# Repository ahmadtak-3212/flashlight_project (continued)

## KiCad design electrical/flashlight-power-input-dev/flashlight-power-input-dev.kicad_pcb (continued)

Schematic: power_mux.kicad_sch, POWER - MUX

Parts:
C_U13_1, C_U13_2, C_U17_2, C_U17_3: 1u; C_0402_1005Metric; LCSC C1525
C_U14_1: 100n; C_0402_1005Metric; LCSC C1525
C_U16_1, C_U16_2: 10u; C_0603_1608Metric; LCSC C1525
D_Q1_1, D_Q2_1: GREEN; LED_0603_1608Metric; LCSC C2286
L_U16_1: 4.7u; IND-SMD_L3.0-W3.0_SMNR3015; MPN SMNR3015-4R7MT; LCSC Part C23960
Q1, Q2: 2N7002; SOT-23
R_Q1_1, R_Q2_1: 1k; R_0402_1005Metric; LCSC C25091
R_U14_1: 100; R_0603_1608Metric_Pad0.98x0.95mm_HandSolder; LCSC C25091
R_U16_1: 0; R_0603_1608Metric_Pad0.98x0.95mm_HandSolder; LCSC C25091
R_U16_2: DNP; R_0603_1608Metric_Pad0.98x0.95mm_HandSolder; LCSC C25091; not fitted
U13, U15: CSD16406Q3; TRANS_CSD16406Q3
U14, U17: LM5050-1; TSOT-23-6
U16: TPS61222DCK; Texas_R-PDSO-G6

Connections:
/Project Architecture/POWER - BATTERY/VBAT_P: C_U16_1.1, C_U17_2.1, D_Q1_1.2 (A), D_Q2_1.2 (A), L_U16_1.1, U15.1, U15.2, U15.3, U16.1 (VIN), U16.6 (EN), U17.4 (IN); also elsewhere on the board
/Project Architecture/POWER - CHARGER/V_PD: C_U13_1.1, U13.1, U13.2, U13.3, U14.4 (IN); also elsewhere on the board
/Project Architecture/POWER - MUX/PD_SEL: Q2.1 (G), U13.4, U14.5 (GATE)
/Project Architecture/POWER - MUX/VBAT_SEL: Q1.1 (G), U15.4, U17.5 (GATE)
/Project Architecture/POWER - MUX/VBAT_VS_BIAS: C_U16_2.1, R_U16_1.2, U16.4 (VOUT), U17.1 (VS)
/Project Architecture/POWER - MUX/V_SYS_OUT: C_U13_2.1, C_U17_3.1, R_U14_1.1, U13.5, U13.6, U13.7, U13.8, U14.6 (OUT), U15.5, U15.6, U15.7, U15.8, U17.6 (OUT); also elsewhere on the board
GND: C_U13_1.2, C_U13_2.2, C_U14_1.2, C_U16_1.2, C_U16_2.2, C_U17_2.2, C_U17_3.2, Q1.2 (S), Q2.2 (S), R_U16_2.2, U14.2 (GND), U16.3 (GND), U17.2 (GND); also elsewhere on the board
unnamed: D_Q1_1.1 (K), R_Q1_1.1
unnamed: D_Q2_1.1 (K), R_Q2_1.1
unnamed: Q1.3 (D), R_Q1_1.2
unnamed: Q2.3 (D), R_Q2_1.2
unnamed: C_U14_1.1, R_U14_1.2, U14.1 (VS)
unnamed: R_U16_1.1, R_U16_2.1, U16.2 (FB)
unnamed: L_U16_1.2, U16.5 (L)

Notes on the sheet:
BQ25303J Datasheet
TPS61222 BIAS VOLTAGE
LM5050-1 POWER MUX
LED CHARGE INDICATOR
[${#}] ${TITLE}

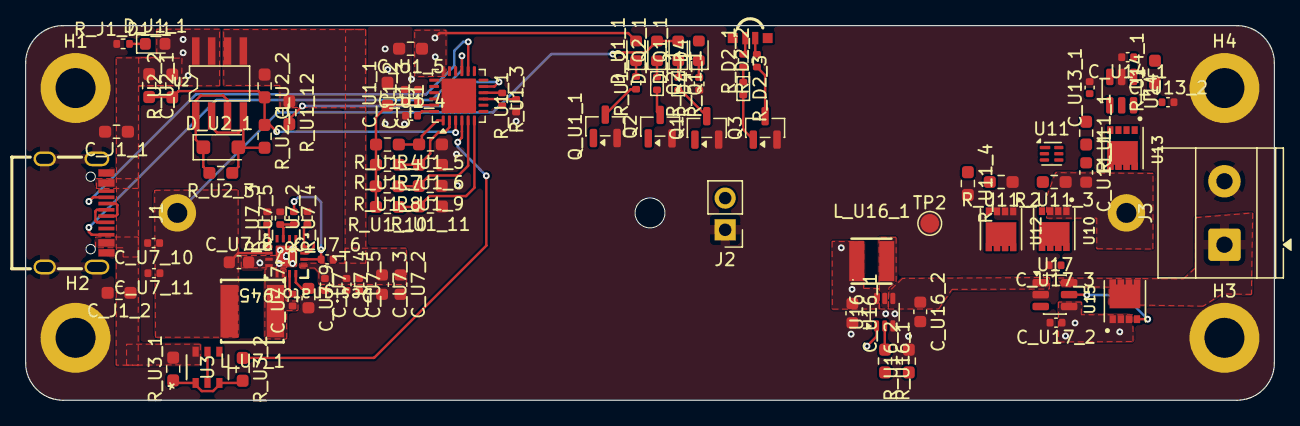
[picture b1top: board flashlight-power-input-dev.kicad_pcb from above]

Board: 4 copper layers, 100.0 x 30.0 mm, 97 parts (1 on the bottom side), 55 nets.

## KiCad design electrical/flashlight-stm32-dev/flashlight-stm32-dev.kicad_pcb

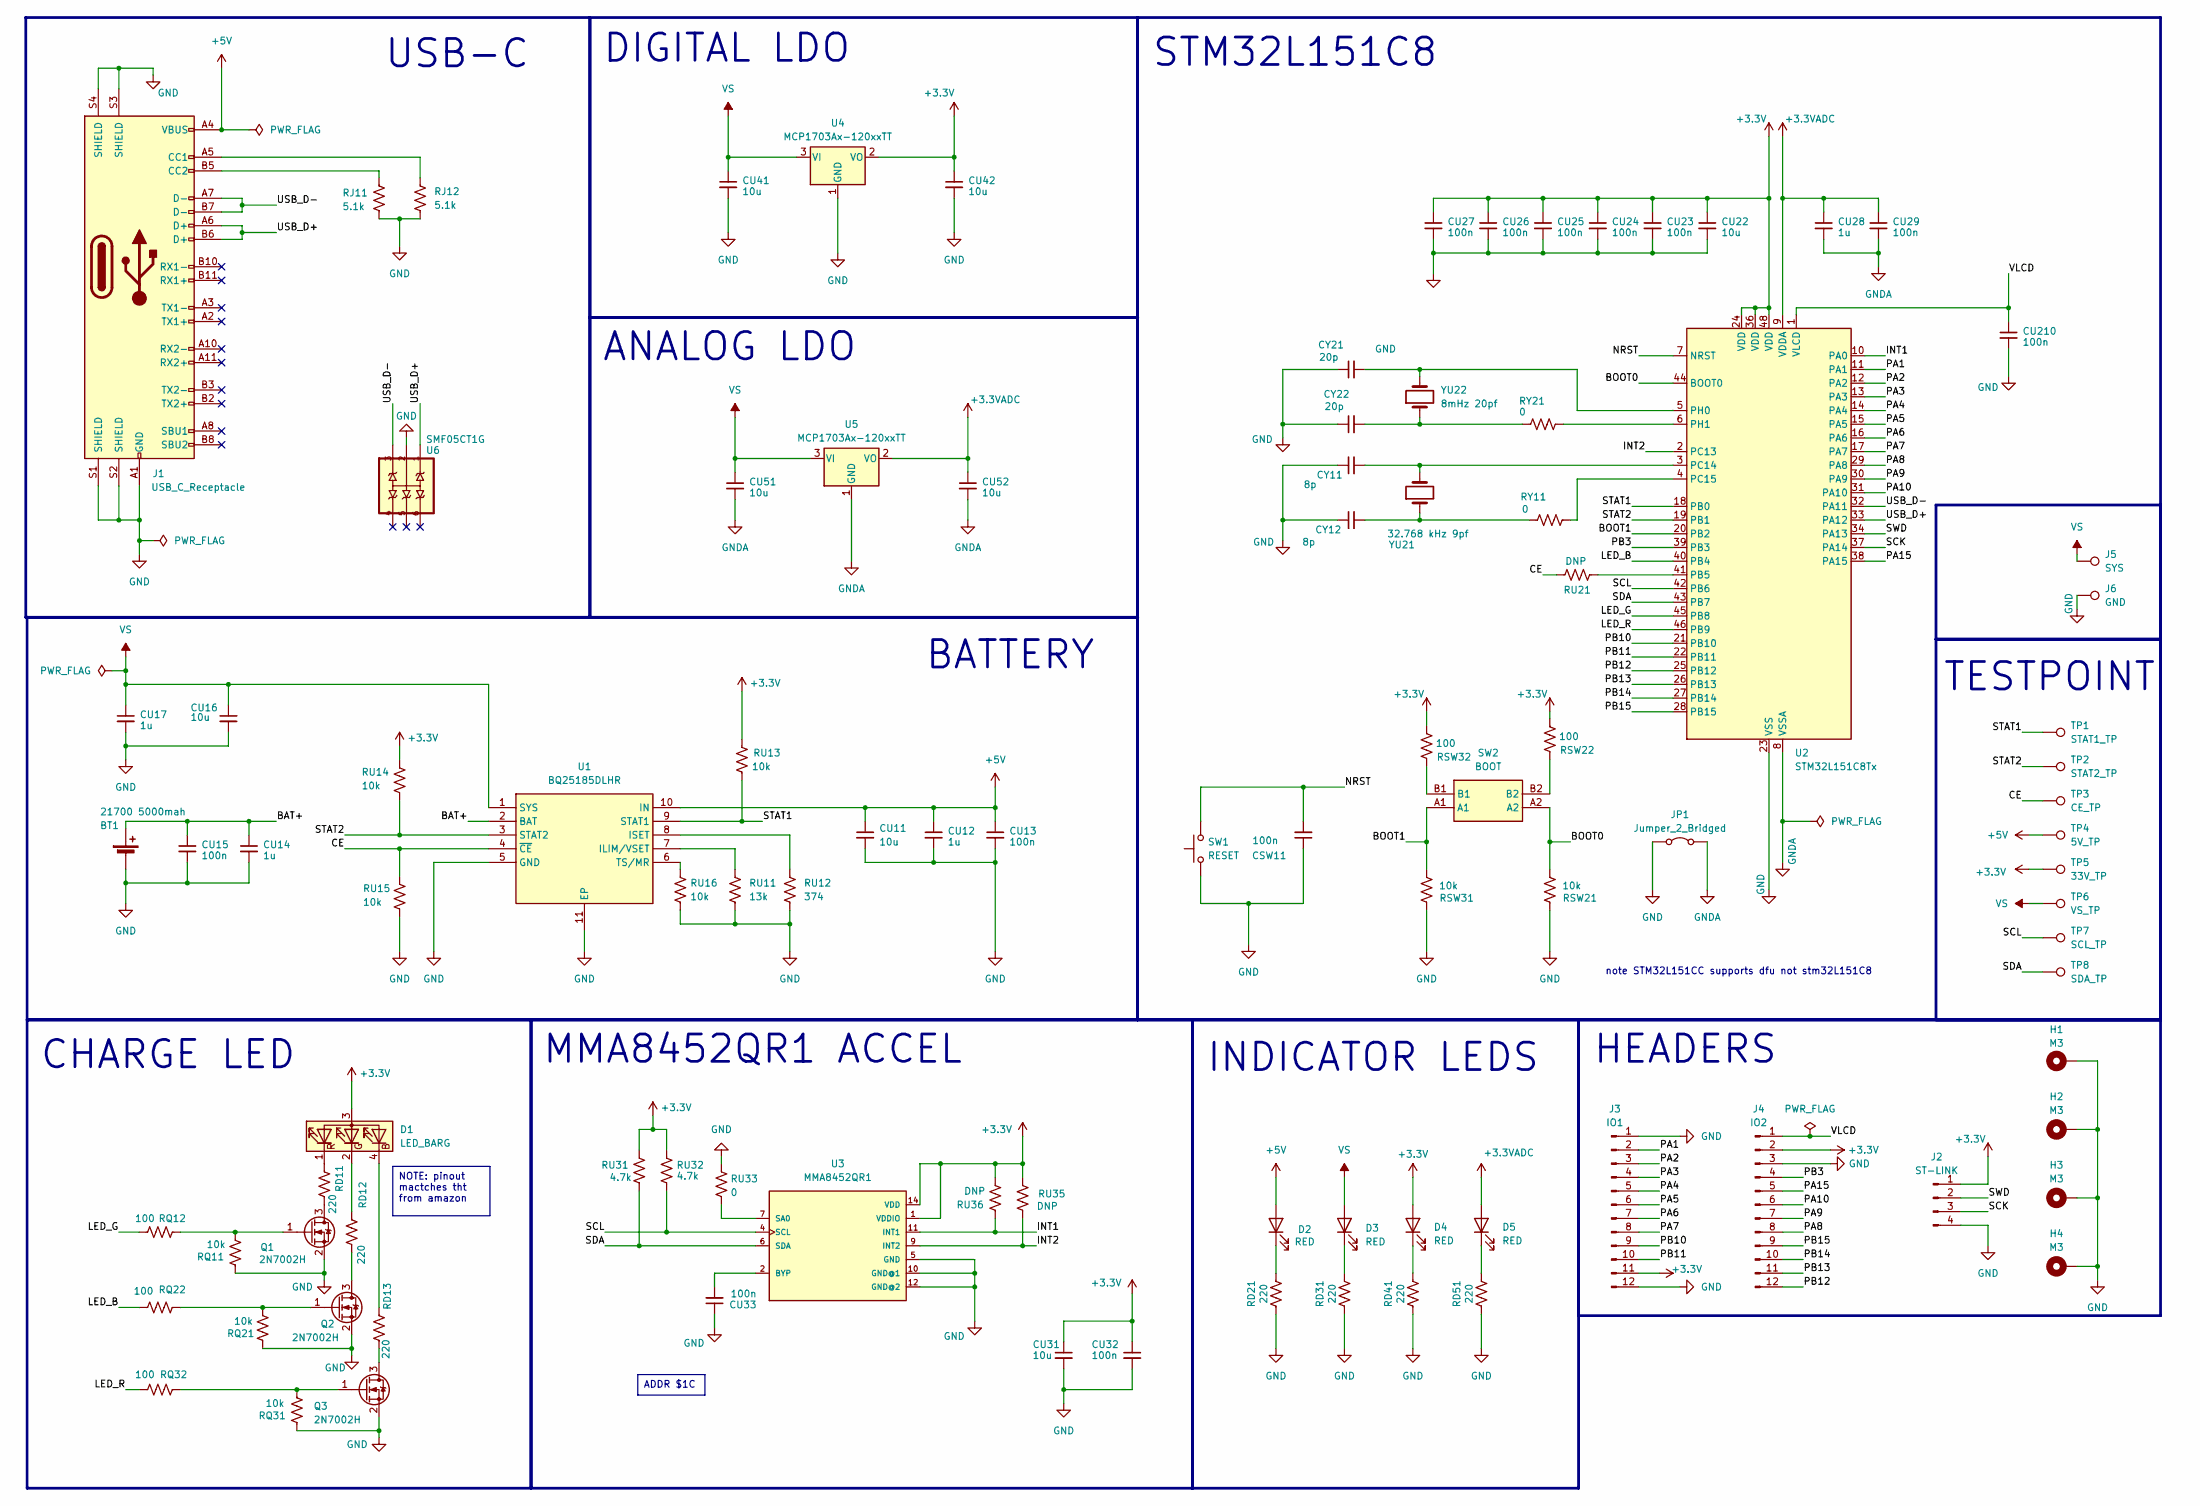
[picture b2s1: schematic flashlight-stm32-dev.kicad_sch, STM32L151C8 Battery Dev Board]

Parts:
BT1: 21700 5000mah; BISTOOK_BATTERY_HOLDER_21700
CSW11: 100n; C_0402_1005Metric; LCSC C1525
CU11, CU22, CU31, CU41, CU42, CU51, CU52: 10u; C_0603_1608Metric; LCSC C96446
CU12, CU28: 1u; C_0603_1608Metric; LCSC C15849
CU13, CU15, CU23, CU24, CU25, CU26, CU27, CU29, CU32, CU33: 100n; C_0402_1005Metric; LCSC C1525
CU14: 1u; C_0402_1005Metric; LCSC C52923
CU16: 10u; C_0603_1608Metric; LCSC C15849
CU17: 1u; C_0402_1005Metric; LCSC C1525
CU210: 100n; C_0603_1608Metric_Pad1.08x0.95mm_HandSolder; LCSC C1525
CY11, CY12: 8p; C_0402_1005Metric; LCSC C1578
CY21, CY22: 20p; C_0402_1005Metric; LCSC C76959
D1: LED_BARG; LED-SMD_4P-L1.6-W1.6-BR-RD
D2, D3, D4, D5: RED; LED_0603_1608Metric; LCSC C2286
H1, H2, H3, H4: M3; MountingHole_2.7mm_Pad
J1: USB_C_Receptacle; AMPHENOL_12401832E402A; LCSC C464604
J2: ST-LINK; PinHeader_1x04_P2.54mm_Vertical
J3: IO1; PinHeader_1x12_P2.54mm_Vertical
J4: IO2; PinHeader_1x12_P2.54mm_Vertical
J5: SYS; Pin_D1.3mm_L11.0mm
J6: GND; Pin_D1.3mm_L11.0mm
JP1: Jumper_2_Bridged; SolderJumper-2_P1.3mm_Bridged_RoundedPad1.0x1.5mm
Q1, Q2, Q3: 2N7002H; SOT-23_Handsoldering; LCSC C8545
RD11, RD12, RD13, RD21, RD31, RD41, RD51: 220; R_0402_1005Metric; LCSC C25091
RJ11: 5.1k; R_0402_1005Metric; LCSC C25905
RJ12: 5.1k; R_0402_1005Metric; LCSC C25768
RQ11, RQ21, RQ31: 10k; R_0402_1005Metric; LCSC C25744
RQ12, RQ22, RQ32: 100; R_0402_1005Metric; LCSC C25076
RSW21, RSW31: 10k; R_0402_1005Metric; LCSC C25744
RSW22, RSW32: 100; R_0402_1005Metric; LCSC C25076
RU11: 13k; R_0603_1608Metric_Pad0.98x0.95mm_HandSolder; LCSC C22797
RU12: 374; R_0603_1608Metric_Pad0.98x0.95mm_HandSolder; LCSC C23149
RU13, RU14, RU15: 10k; R_0402_1005Metric; LCSC C25744
RU16: 10k; R_0603_1608Metric_Pad0.98x0.95mm_HandSolder; LCSC C25804
RU21: DNP; R_0603_1608Metric_Pad0.98x0.95mm_HandSolder
RU31, RU32: 4.7k; R_0402_1005Metric; LCSC C25744
RU33: 0; R_0603_1608Metric_Pad0.98x0.95mm_HandSolder; LCSC C21189
RU35, RU36: DNP; R_0603_1608Metric_Pad0.98x0.95mm_HandSolder; LCSC C25744
RY11, RY21: 0; R_0603_1608Metric_Pad0.98x0.95mm_HandSolder; LCSC C21189
SW1: RESET; TS1187ABAB; LCSC C318884
SW2: BOOT; 2182LPSTR; Manufacturer_Part_Number 218-2LPSTR; Mouser Part Number 774-2182LPSTR
TP1: STAT1_TP; TestPoint_Pad_D2.0mm
TP2: STAT2_TP; TestPoint_Pad_D2.0mm
TP3: CE_TP; TestPoint_Pad_D2.0mm
TP4: 5V_TP; TestPoint_Pad_D2.0mm
TP5: 33V_TP; TestPoint_Pad_D2.0mm
TP6: VS_TP; TestPoint_Pad_D2.0mm
TP7: SCL_TP; TestPoint_Pad_D2.0mm
TP8: SDA_TP; TestPoint_Pad_D2.0mm
U1: BQ25185DLHR; SON40P220X200X80-11N; Manufacturer_Part_Number BQ25185DLHR; Mouser Part Number 595-BQ25185DLHR
U2: STM32L151C8Tx; LQFP-48_7x7mm_P0.5mm; LCSC C95578
U3: MMA8452QR1; PQFN50P300X300X100-16N
U4, U5: MCP1703Ax-120xxTT; SOT-23_Handsoldering; LCSC C5446
U6: SMF05CT1G; SOT65P210X110-6N; LCSC C15879
YU21: 32.768 kHz 9pf; Crystal_SMD_2012-2Pin_2.0x1.2mm; LCSC C96341
YU22: 8mHz 20pf; Crystal_SMD_5032-2Pin_5.0x3.2mm; LCSC C115962

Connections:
+3.3V: CU22.1, CU23.1, CU24.1, CU25.1, CU26.1, CU27.1, CU31.1, CU32.1, CU42.1, D1.3 (A), D4.2 (A), J2.1, J3.11, J4.2, RSW22.1, RSW32.1, RU13.2, RU14.2, RU31.2, RU32.2, RU35.2, RU36.1, TP5.1, U2.24 (VDD), U2.36 (VDD), U2.48 (VDD), U3.1 (VDDIO), U3.14 (VDD), U4.2 (VO)
+3.3VADC: CU28.1, CU29.1, CU52.1, D5.2 (A), U2.9 (VDDA), U5.2 (VO)
+5V: CU11.1, CU12.1, CU13.1, D2.2 (A), J1.A4 (VBUS), J1.A9 (VBUS), J1.B4 (VBUS), J1.B9 (VBUS), TP4.1, U1.10 (IN)
/BAT+: BT1.1 (+), CU14.1, CU15.1, U1.2 (BAT)
/BOOT0: RSW21.2, SW2.A2, U2.44 (BOOT0)
/BOOT1: RSW31.2, SW2.A1, U2.20 (PB2)
/CE: RU15.2, RU21.2, TP3.1, U1.4 (~CE)
/INT1: RU36.2, U2.10 (PA0), U3.11 (INT1)
/INT2: RU35.1, U2.2 (PC13), U3.9 (INT2)
/LED_B: RQ22.1, U2.40 (PB4)
/LED_G: RQ12.1, U2.45 (PB8)
/LED_R: RQ32.1, U2.46 (PB9)
/NRST: CSW11.2, SW1.2, U2.7 (NRST)
/PA1: J3.2, U2.11 (PA1)
/PA2: J3.3, U2.12 (PA2)
/PA3: J3.4, U2.13 (PA3)
/PA4: J3.5, U2.14 (PA4)
/PA5: J3.6, U2.15 (PA5)
/PA6: J3.7, U2.16 (PA6)
/PA7: J3.8, U2.17 (PA7)
/PA8: J4.8, U2.29 (PA8)
/PA9: J4.7, U2.30 (PA9)
/PA10: J4.6, U2.31 (PA10)
/PA15: J4.5, U2.38 (PA15)
/PB3: J4.4, U2.39 (PB3)
/PB10: J3.9, U2.21 (PB10)
/PB11: J3.10, U2.22 (PB11)
/PB12: J4.12, U2.25 (PB12)
/PB13: J4.11, U2.26 (PB13)
/PB14: J4.10, U2.27 (PB14)
/PB15: J4.9, U2.28 (PB15)
/SCK: J2.3, U2.37 (PA14)
/SCL: RU32.1, TP7.1, U2.42 (PB6), U3.4 (SCL)
/SDA: RU31.1, TP8.1, U2.43 (PB7), U3.6 (SDA)
/STAT1: RU13.1, TP1.1, U1.9 (STAT1), U2.18 (PB0)
/STAT2: RU14.1, TP2.1, U1.3 (STAT2), U2.19 (PB1)
/SWD: J2.2, U2.34 (PA13)
/USB_D+: J1.A6 (D+), J1.B6 (D+), U2.33 (PA12), U6.1
/USB_D-: J1.A7 (D-), J1.B7 (D-), U2.32 (PA11), U6.3
/VLCD: CU210.1, J4.1, U2.1 (VLCD)
GND: BT1.2 (-), CSW11.1, CU11.2, CU12.2, CU13.2, CU14.2, CU15.2, CU16.2, CU17.2, CU22.2, CU23.2, CU24.2, CU25.2, CU26.2, CU27.2, CU31.2, CU32.2, CU33.1, CU41.2, CU42.2, CU210.2, CY11.1, CY12.1, CY21.1, CY22.1, H1.1, H2.1, H3.1, H4.1, J1.A1 (GND), J1.A12 (GND), J1.B1 (GND), J1.B12 (GND), J1.S1 (SHIELD), J1.S2 (SHIELD), J1.S3 (SHIELD), J1.S4 (SHIELD), J2.4, J3.1, J3.12, J4.3, J6.1, JP1.1 (A), Q1.2 (S), Q2.2 (S), Q3.2 (S), RD21.1, RD31.1, RD41.1, RD51.1, RJ11.2, RJ12.1, RQ11.1, RQ21.1, RQ31.1, RSW21.1, RSW31.1, RU11.1, RU12.1, RU15.1, RU16.1, RU33.1, SW1.1, U1.5 (GND), U1.11 (EP), U2.23 (VSS), U2.35 (VSS), U2.47 (VSS), U3.5 (GND), U3.10 (GND@1), U3.12 (GND@2), U4.1 (GND), U6.2
GNDA: CU28.2, CU29.2, CU51.2, CU52.2, JP1.2 (B), U2.8 (VSSA), U5.1 (GND)
unnamed: CY12.2, RY11.2, YU21.1
unnamed: CY22.2, RY21.2, YU22.1
unnamed: D1.4 (BK), RD13.2
unnamed: D1.2 (GK), RD12.2
unnamed: D1.1 (RK), RD11.2
unnamed: D2.1 (K), RD21.2
unnamed: D3.1 (K), RD31.2
unnamed: D4.1 (K), RD41.2
unnamed: D5.1 (K), RD51.2
unnamed: J1.A5 (CC1), RJ12.2
unnamed: J1.B5 (CC2), RJ11.1
unnamed: Q1.3 (D), RD11.1
unnamed: Q1.1 (G), RQ11.2, RQ12.2
unnamed: Q2.3 (D), RD12.1
unnamed: Q2.1 (G), RQ21.2, RQ22.2
unnamed: Q3.3 (D), RD13.1
unnamed: Q3.1 (G), RQ31.2, RQ32.2
unnamed: RSW22.2, SW2.B2
unnamed: RSW32.2, SW2.B1
unnamed: RU11.2, U1.7 (ILIM/VSET)
unnamed: RU12.2, U1.8 (ISET)
unnamed: RU16.2, U1.6 (TS/MR)
unnamed: RU21.1, U2.41 (PB5)
unnamed: CY11.2, U2.3 (PC14), YU21.2
unnamed: RY11.1, U2.4 (PC15)
unnamed: CY21.2, U2.5 (PH0), YU22.2
unnamed: RY21.1, U2.6 (PH1)
unnamed: CU33.2, U3.2 (BYP)
unnamed: RU33.2, U3.7 (SA0)
VS: CU16.1, CU17.1, CU41.1, CU51.1, D3.2 (A), J5.1, TP6.1, U1.1 (SYS), U4.3 (VI), U5.3 (VI)

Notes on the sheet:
NOTE: pinout mactches tht from amazon
ADDR $1C
USB-C
note STM32L151CC supports dfu not stm32L151C8
HEADERS
ANALOG LDO
MMA8452QR1 ACCEL
TESTPOINT
DIGITAL LDO
BATTERY
CHARGE LED
INDICATOR LEDS
STM32L151C8

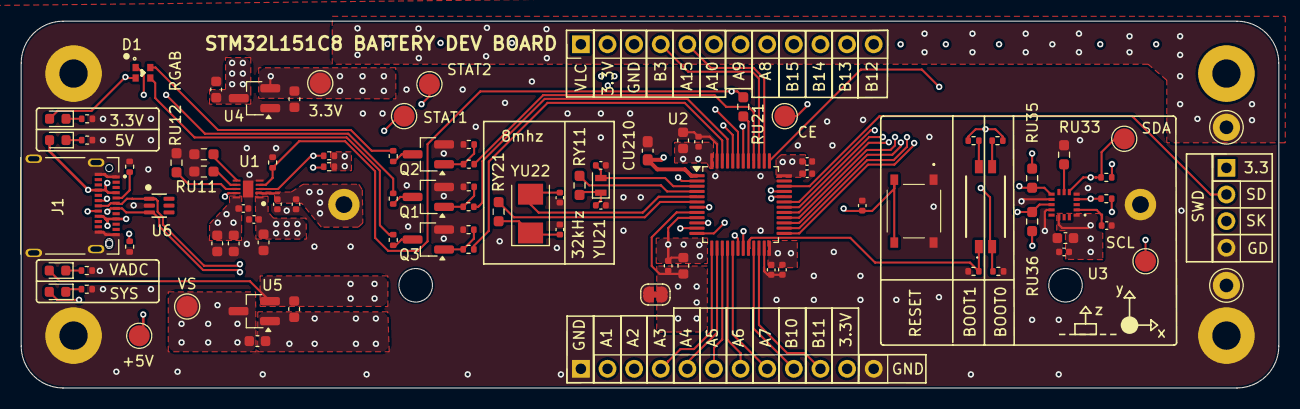
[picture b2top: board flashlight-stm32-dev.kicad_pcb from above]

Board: 6 copper layers, 120.0 x 35.0 mm, 99 parts (1 on the bottom side), 72 nets.

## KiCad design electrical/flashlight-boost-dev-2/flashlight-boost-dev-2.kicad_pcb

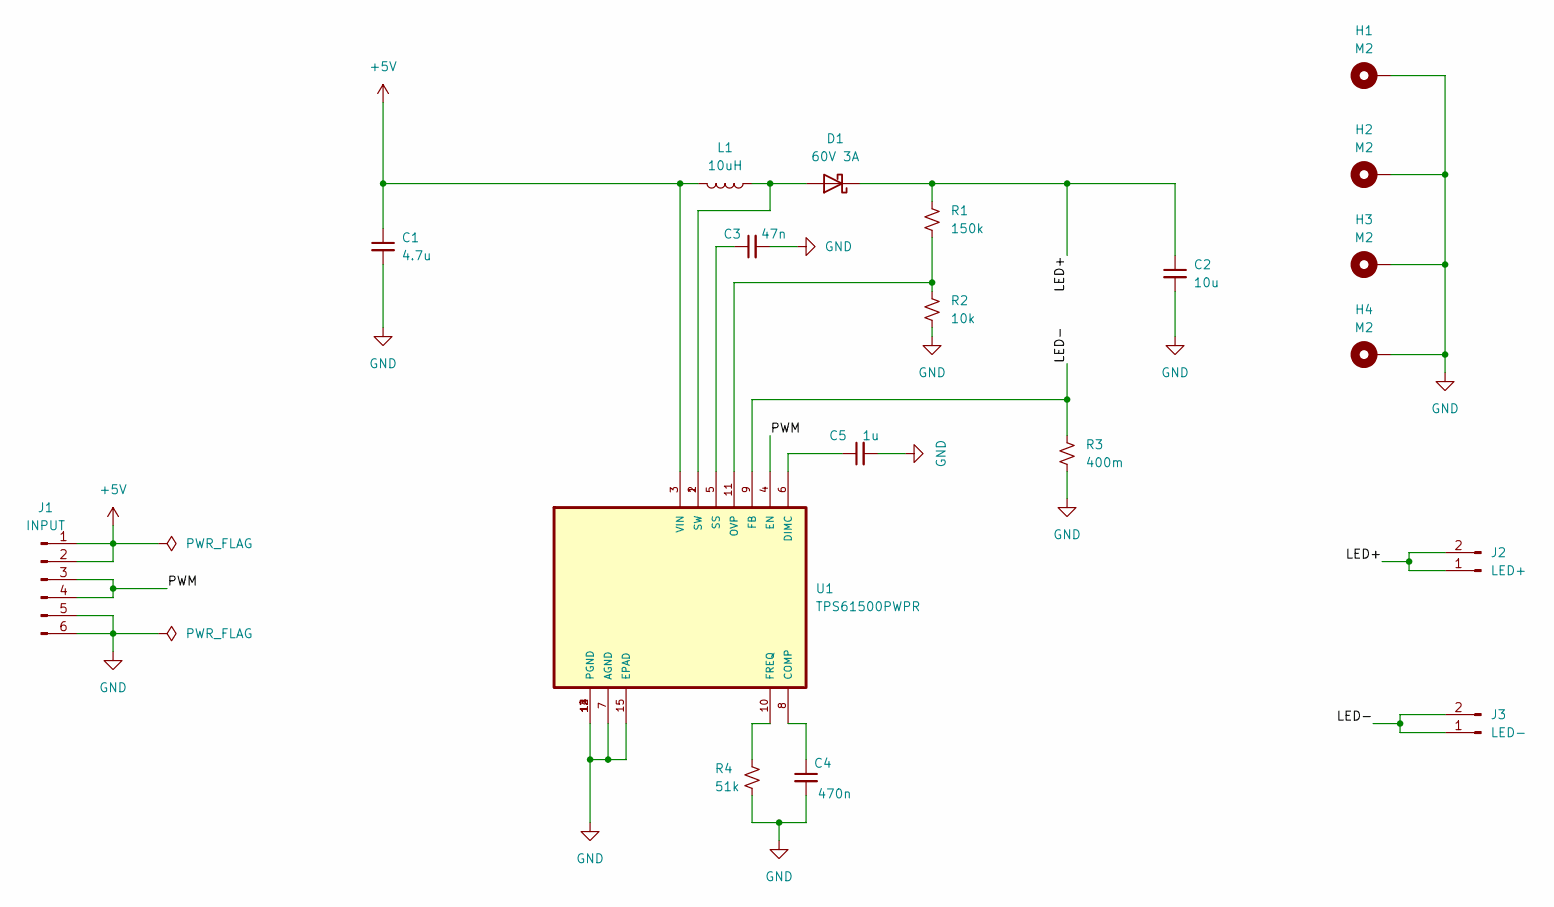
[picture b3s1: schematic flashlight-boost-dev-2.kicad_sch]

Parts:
C1: 4.7u; C_0603_1608Metric_Pad1.08x0.95mm_HandSolder; LCSC C19666
C2: 10u; C_0603_1608Metric_Pad1.08x0.95mm_HandSolder; LCSC C96446
C3: 47n; C_0603_1608Metric_Pad1.08x0.95mm_HandSolder; LCSC C1622
C4: 470n; C_0603_1608Metric_Pad1.08x0.95mm_HandSolder; LCSC C1623
C5: 1u; C_0603_1608Metric_Pad1.08x0.95mm_HandSolder; LCSC C15849
D1: 60V 3A; DIOM7959X262N; LCSC C35722
H1, H2, H3, H4: M2; MountingHole_2.5mm_Pad
J1: INPUT; PinHeader_1x06_P2.54mm_Vertical
J2: LED+; PinHeader_1x02_P2.54mm_Vertical
J3: LED-; PinHeader_1x02_P2.54mm_Vertical
L1: 10uH; L_10.4x10.4_H4.8; LCSC C171589
R1: 150k; R_0603_1608Metric_Pad0.98x0.95mm_HandSolder; LCSC C22807
R2: 10k; R_0603_1608Metric_Pad0.98x0.95mm_HandSolder; LCSC C25804
R3: 400m; R_0603_1608Metric_Pad0.98x0.95mm_HandSolder; LCSC C57344
R4: 51k; R_0603_1608Metric_Pad0.98x0.95mm_HandSolder; LCSC C23196
U1: TPS61500PWPR; IC_TPS27S100BPWPR; LCSC C71160

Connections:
+5V: C1.1, J1.1, J1.2, L1.2, U1.3 (VIN)
/LED+: C2.1, D1.1 (K), J2.1, J2.2, R1.1
/LED-: J3.1, J3.2, R3.1, U1.9 (FB)
/PWM: J1.3, J1.4, U1.4 (EN)
GND: C1.2, C2.2, C3.2, C4.2, C5.2, H1.1, H2.1, H3.1, H4.1, J1.5, J1.6, R2.2, R3.2, R4.2, U1.7 (AGND), U1.12 (PGND), U1.13 (PGND), U1.14 (PGND), U1.15 (EPAD)
unnamed: D1.2 (A), L1.1, U1.1 (SW), U1.2 (SW)
unnamed: C4.1, U1.8 (COMP)
unnamed: C5.1, U1.6 (DIMC)
unnamed: R4.1, U1.10 (FREQ)
unnamed: R1.2, R2.1, U1.11 (OVP)
unnamed: C3.1, U1.5 (SS)

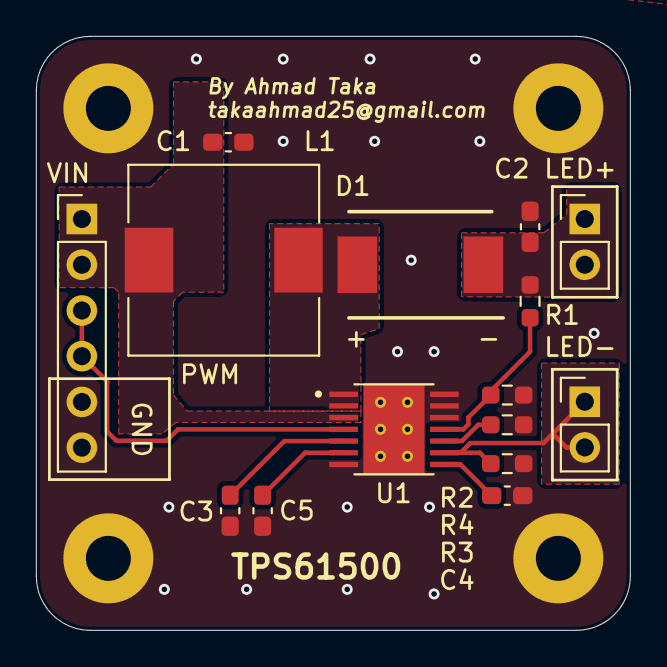
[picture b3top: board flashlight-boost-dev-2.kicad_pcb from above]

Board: 2 copper layers, 33.0 x 33.0 mm, 19 parts (0 on the bottom side), 11 nets.

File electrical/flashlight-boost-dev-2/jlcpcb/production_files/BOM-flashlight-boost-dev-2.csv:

Comment,Designator,Footprint,LCSC,Quantity
1u,C5,C_0603_1608Metric_Pad1.08x0.95mm_HandSolder,C15849,1
47n,C3,C_0603_1608Metric_Pad1.08x0.95mm_HandSolder,C1622,1
470n,C4,C_0603_1608Metric_Pad1.08x0.95mm_HandSolder,C1623,1
10uH,L1,L_10.4x10.4_H4.8,C171589,1
4.7u,C1,C_0603_1608Metric_Pad1.08x0.95mm_HandSolder,C19666,1
150k,R1,R_0603_1608Metric_Pad0.98x0.95mm_HandSolder,C22807,1
51k,R4,R_0603_1608Metric_Pad0.98x0.95mm_HandSolder,C23196,1
10k,R2,R_0603_1608Metric_Pad0.98x0.95mm_HandSolder,C25804,1
60V 3A,D1,DIOM7959X262N,C35722,1
400m,R3,R_0603_1608Metric_Pad0.98x0.95mm_HandSolder,C57344,1
TPS61500PWPR,U1,IC_TPS27S100BPWPR,C71160,1
10u,C2,C_0603_1608Metric_Pad1.08x0.95mm_HandSolder,C96446,1

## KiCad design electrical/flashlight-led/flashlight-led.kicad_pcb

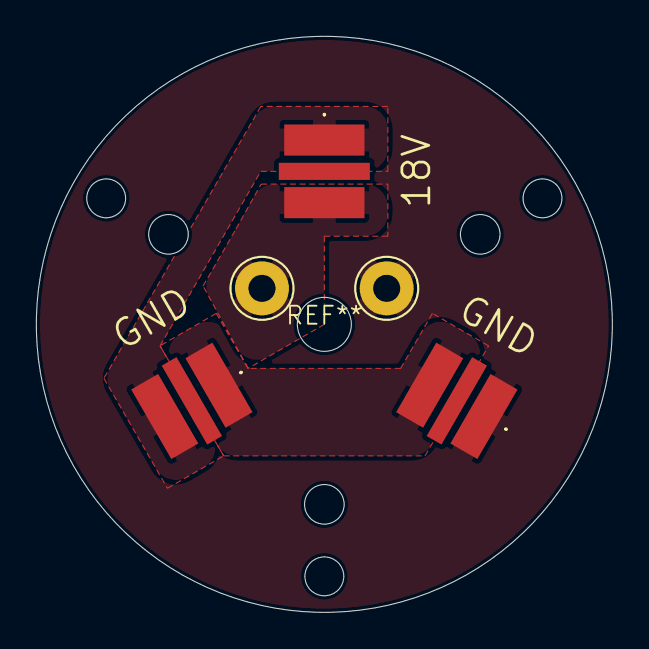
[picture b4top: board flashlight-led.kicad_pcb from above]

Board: 2 copper layers, 32.0 x 32.0 mm, 8 parts (0 on the bottom side), 4 nets, no tracks yet.

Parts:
D1, D2, D3: LED_WARM; JR5050CWTEB30EB0000N0000001
H1, H2, H3: MountingHole; MountingHole_2.2mm_M2
J1: +18V; TestPoint_THTPad_D3.0mm_Drill1.5mm
J3: GND; TestPoint_THTPad_D3.0mm_Drill1.5mm

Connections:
+18V: D1.2 (A), J1.1
/D12: D1.1 (K), D2.2 (A)
/D23: D2.1 (K), D3.2 (A)
GND: D3.1 (K), J3.1

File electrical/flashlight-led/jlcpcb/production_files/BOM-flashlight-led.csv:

Comment,Designator,Footprint,LCSC,Quantity
GND,J3,TestPoint_THTPad_D3.0mm_Drill1.5mm,,1
GND,J2,TestPoint_THTPad_D3.0mm_Drill1.5mm,,1
+18V,J1,TestPoint_THTPad_D3.0mm_Drill1.5mm,,1
LED_WARM,D1,JR5050CWTEB30EB0000N0000001,,1
LED_WARM,D2,JR5050CWTEB30EB0000N0000001,,1
LED_WARM,D3,JR5050CWTEB30EB0000N0000001,,1

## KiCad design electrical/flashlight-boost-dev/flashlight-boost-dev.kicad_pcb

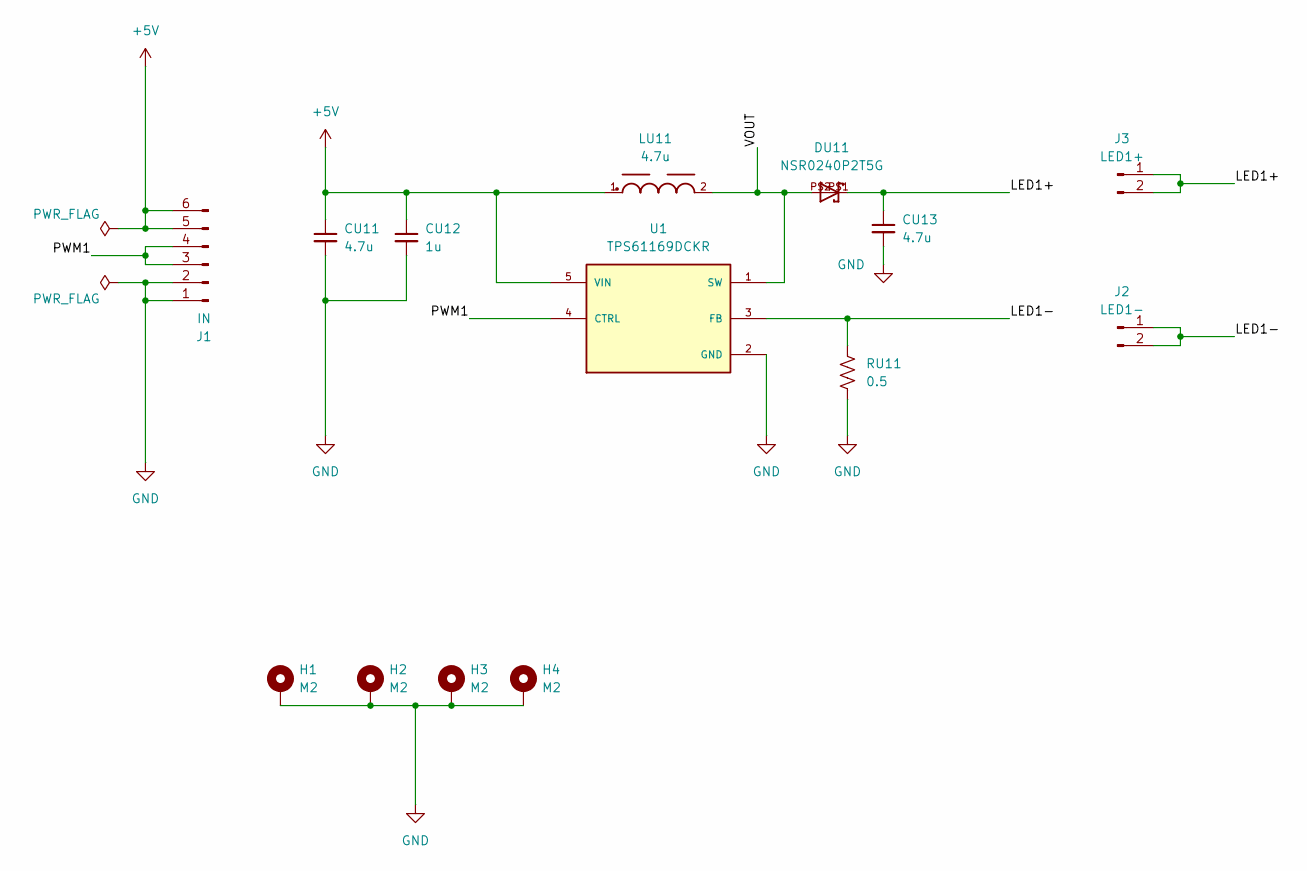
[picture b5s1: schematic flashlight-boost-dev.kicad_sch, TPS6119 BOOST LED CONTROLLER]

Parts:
CU11, CU13: 4.7u; C_0805_2012Metric_Pad1.18x1.45mm_HandSolder
CU12: 1u; C_0603_1608Metric
DU11: NSR0240P2T5G; SOD-923
H1, H2, H3, H4: M2; MountingHole_2.2mm_M2_Pad
J1: IN; PinHeader_1x06_P2.54mm_Vertical
J2: LED1-; PinHeader_1x02_P2.54mm_Vertical
J3: LED1+; PinHeader_1x02_P2.54mm_Vertical
LU11: 4.7u; WE-MAPI_4030
RU11: 0.5; R_1206_3216Metric_Pad1.30x1.75mm_HandSolder
U1: TPS61169DCKR; SOT65P210X110-5N; PARTREV A

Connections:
+5V: CU11.1, CU12.1, J1.5, J1.6, LU11.1, U1.5 (VIN)
/LED1+: CU13.1, DU11.P$1, J3.1, J3.2
/LED1-: J2.1, J2.2, RU11.1, U1.3 (FB)
/PWM1: J1.3, J1.4, U1.4 (CTRL)
/VOUT: DU11.P$2, LU11.2, U1.1 (SW)
GND: CU11.2, CU12.2, CU13.2, H1.1, H2.1, H3.1, H4.1, J1.1, J1.2, RU11.2, U1.2 (GND)

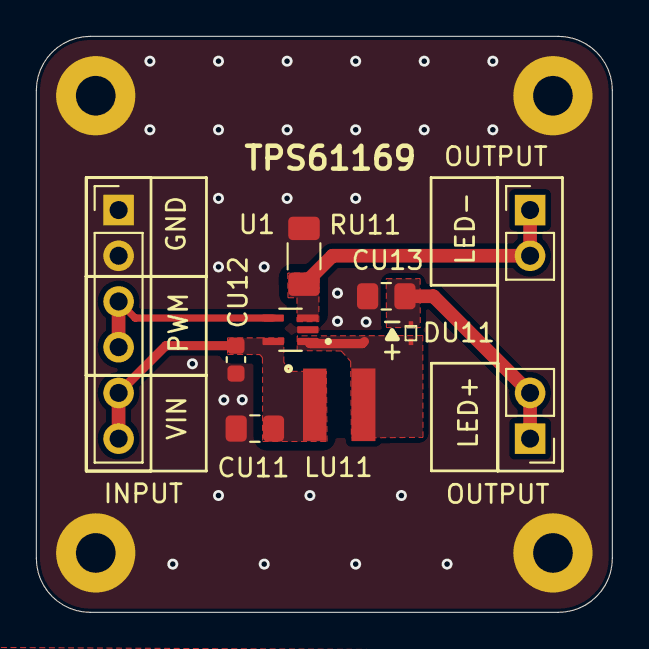
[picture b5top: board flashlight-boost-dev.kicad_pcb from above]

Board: 2 copper layers, 32.0 x 32.0 mm, 14 parts (0 on the bottom side), 6 nets.

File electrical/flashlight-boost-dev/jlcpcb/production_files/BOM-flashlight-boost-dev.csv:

Comment,Designator,Footprint,LCSC,Quantity
1u,CU12,C_0603_1608Metric,C15849,1
4.7u,"CU11,CU13",C_0805_2012Metric_Pad1.18x1.45mm_HandSolder,C1779,2
0.5,RU11,R_1206_3216Metric_Pad1.30x1.75mm_HandSolder,C25340,1
WE-MAPI_4030,LU11,WE-MAPI_4030,C6707914,1
TPS61169DCKR,U1,SOT65P210X110-5N,C71045,1
NSR0240P2T5G,DU11,SOD-923,C896425,1

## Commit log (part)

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2025-02-16 init
2025-02-17 with headers
2025-02-17 jlc init
2025-02-18 updated accel and usbc cc
2025-02-19 final for review
2025-04-01 jlc result
2025-04-03 added firmware
2025-04-21 full init
2025-04-24 TPS61088 added to lib
2025-04-26 full new
